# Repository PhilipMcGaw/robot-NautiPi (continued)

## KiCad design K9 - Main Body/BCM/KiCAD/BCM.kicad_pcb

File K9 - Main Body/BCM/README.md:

# K9 Body Control Module (BCM)

## Purpose

Describe the Body Control Module (BCM) hardware, firmware, interfaces, and supporting engineering material contained in this directory.

## Scope

This directory is part of the physical hardware design for K9 within `robot-NautiPi`.

- **NautiPi** is the source of truth for physical hardware design.
- **CuttleOS** is the source of truth for system software, deployment, and runtime behaviour.
- **SquidLink** is used for ROS 2/Gazebo simulation and integration testing.
- **Chartroom** provides the project-wide documentation and repository conventions.

## Contents

Document the files and subdirectories contained here, including their purpose and any significant design or implementation constraints.

## Interfaces

Document important electrical, mechanical, communications, and software interfaces. Include connector names, signal names, protocols, voltage levels, or other interface information where applicable.

## Dependencies

Record dependencies on other hardware assemblies, firmware, software, libraries, or external components where they materially affect this module.

## Status

Use explicit evidence-based status terms such as:

- `planned`
- `implemented`
- `tested`
- `bench-tested`
- `production-validated`

Do not imply a higher level of validation than the available evidence supports.

## Documentation

Keep this README focused on the purpose and boundaries of the directory. Detailed engineering records should be placed in appropriate documentation files within the project.

## Licence

This material is distributed under the licence stated by the repository root `README.md`. See that file for the current licence and repository-wide documentation policy.

## Related repositories

- [CuttleOS](https://github.com/PhilipMcGaw/robot-CuttleOS) — system software and runtime architecture.
- [SquidLink](https://github.com/PhilipMcGaw/robot-SquidLink) — ROS 2/Gazebo simulation and integration testing.
- [Chartroom](https://github.com/PhilipMcGaw/robot-ChartRoom) — project documentation and engineering context, where applicable.

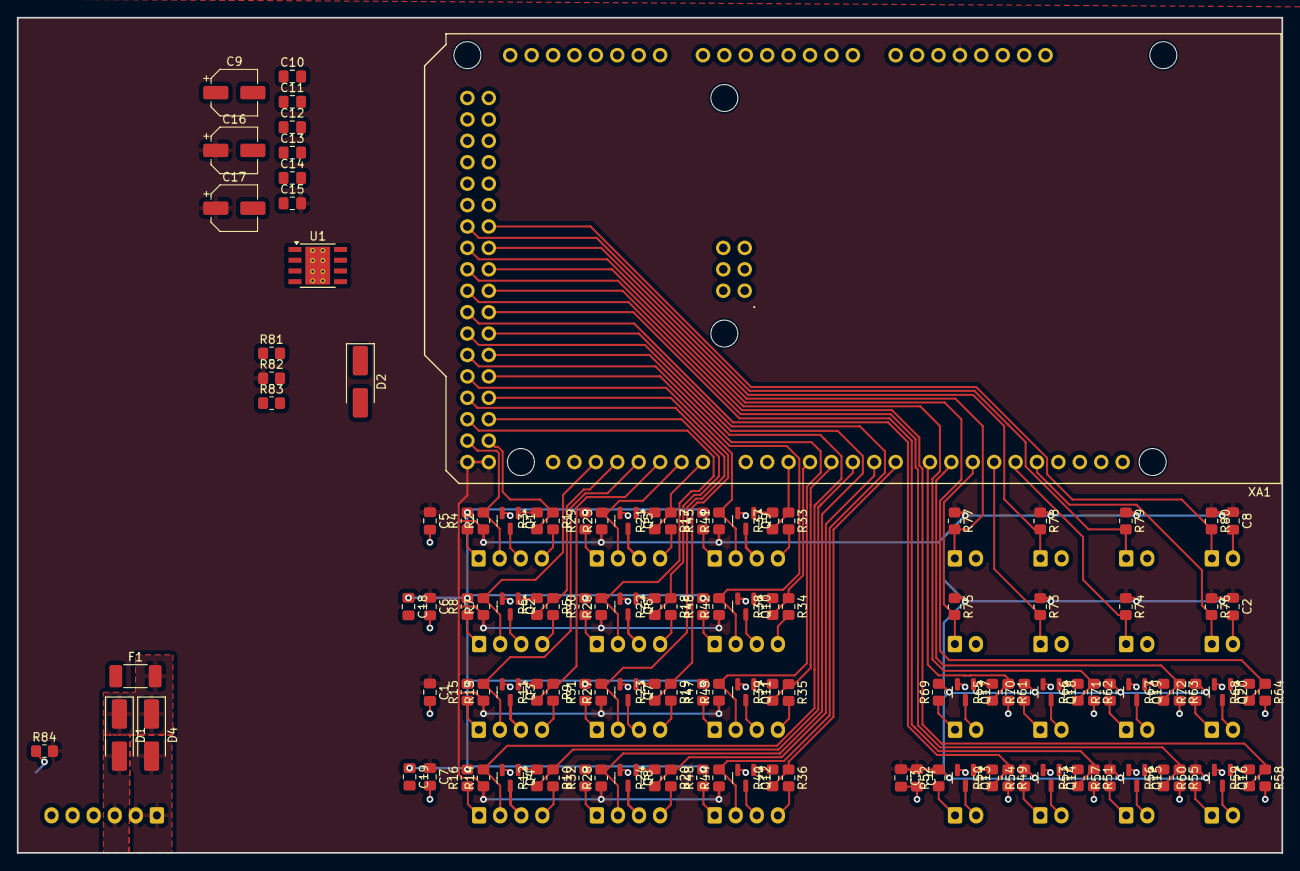
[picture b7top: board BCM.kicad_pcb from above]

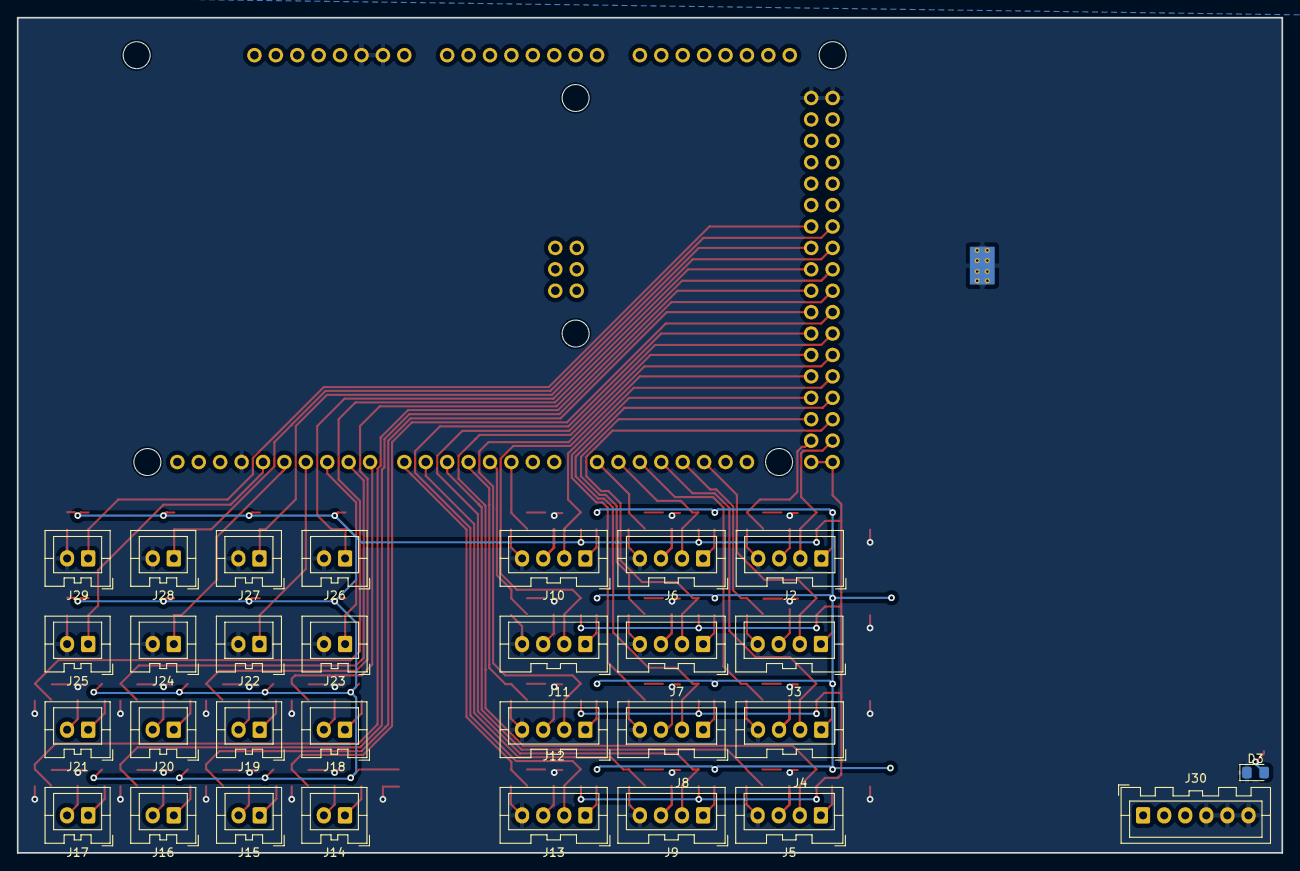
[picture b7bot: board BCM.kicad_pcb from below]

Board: 2 copper layers, 150.0 x 99.1 mm, 159 parts (30 on the bottom side), 114 nets.

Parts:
C1, C2, C3, C4, C5, C6, C7, C8, C18, C19: C_Small; C_0805_2012Metric_Pad1.18x1.45mm_HandSolder
C9: 100μF; CP_Elec_5x5.9
C10: 0.1μF; C_0805_2012Metric_Pad1.18x1.45mm_HandSolder
C11: 10nF; C_0805_2012Metric_Pad1.18x1.45mm_HandSolder
C12: 10pF; C_0805_2012Metric_Pad1.18x1.45mm_HandSolder
C13: 1nF; C_0805_2012Metric_Pad1.18x1.45mm_HandSolder
C14, C15: 0.1uF; C_0805_2012Metric_Pad1.18x1.45mm_HandSolder
C16, C17: 47μF; CP_Elec_5x5.9
D1, D2, D4: SS34; D_SMA_Handsoldering
D3: Green; D_0805_2012Metric_Pad1.15x1.40mm_HandSolder
F1: Fuse; Fuse_2010_5025Metric_Pad1.52x2.65mm_HandSolder
J2: Back_1; JST_XA_B04B-XASK-1_1x04_P2.50mm_Vertical
J3: Back_2; JST_XA_B04B-XASK-1_1x04_P2.50mm_Vertical
J4: Back_3; JST_XA_B04B-XASK-1_1x04_P2.50mm_Vertical
J5: Back_4; JST_XA_B04B-XASK-1_1x04_P2.50mm_Vertical
J6: Back_5; JST_XA_B04B-XASK-1_1x04_P2.50mm_Vertical
J7: Back_6; JST_XA_B04B-XASK-1_1x04_P2.50mm_Vertical
J8: Back_7; JST_XA_B04B-XASK-1_1x04_P2.50mm_Vertical
J9: Back_8; JST_XA_B04B-XASK-1_1x04_P2.50mm_Vertical
J10: Back_9; JST_XA_B04B-XASK-1_1x04_P2.50mm_Vertical
J11: Back_10; JST_XA_B04B-XASK-1_1x04_P2.50mm_Vertical
J12: Back_11; JST_XA_B04B-XASK-1_1x04_P2.50mm_Vertical
J13: Back_12; JST_XA_B04B-XASK-1_1x04_P2.50mm_Vertical
J14: Eye1; JST_XA_B02B-XASK-1_1x02_P2.50mm_Vertical
J15: Eye2; JST_XA_B02B-XASK-1_1x02_P2.50mm_Vertical
J16: Nose; JST_XA_B02B-XASK-1_1x02_P2.50mm_Vertical
J17: S1; JST_XA_B02B-XASK-1_1x02_P2.50mm_Vertical
J18: S2; JST_XA_B02B-XASK-1_1x02_P2.50mm_Vertical
J19: S3; JST_XA_B02B-XASK-1_1x02_P2.50mm_Vertical
J20: S4; JST_XA_B02B-XASK-1_1x02_P2.50mm_Vertical
J21: S5; JST_XA_B02B-XASK-1_1x02_P2.50mm_Vertical
J22: Door2; JST_XA_B02B-XASK-1_1x02_P2.50mm_Vertical
J23: Door1; JST_XA_B02B-XASK-1_1x02_P2.50mm_Vertical
J24: But1; JST_XA_B02B-XASK-1_1x02_P2.50mm_Vertical
J25: But2; JST_XA_B02B-XASK-1_1x02_P2.50mm_Vertical
J26: But3; JST_XA_B02B-XASK-1_1x02_P2.50mm_Vertical
J27: But4; JST_XA_B02B-XASK-1_1x02_P2.50mm_Vertical
J28: But5; JST_XA_B02B-XASK-1_1x02_P2.50mm_Vertical
J29: But6; JST_XA_B02B-XASK-1_1x02_P2.50mm_Vertical
J30: Power; JST_XA_B06B-XASK-1_1x06_P2.50mm_Vertical
Q1, Q2, Q3, Q4, Q5, Q6, Q7, Q8, Q9, Q10, Q11, Q12, Q13, Q14, Q15, Q16, Q17, Q18, Q19, Q20: 2N7002; SOT-23
R1, R2, R5, R7, R9, R10, R13, R14, R17, R18, R19, R20, R25, R26, R27, R28, R33, R34, R35, R36, R41, R42, R43, R44, R49, R51, R55, R58, R61, R62, R63, R64, R73, R74, R75, R76, R77, R78, R79, R80: 10k; R_0805_2012Metric_Pad1.20x1.40mm_HandSolder
R3, R4, R6, R8, R11, R12, R15, R16, R21, R22, R23, R24, R29, R30, R31, R32, R37, R38, R39, R40, R45, R46, R47, R48, R50, R52, R53, R54, R56, R57, R59, R60, R65, R66, R67, R68, R69, R70, R71, R72: 330; R_0805_2012Metric_Pad1.20x1.40mm_HandSolder
R81: 29.4k; R_0805_2012Metric_Pad1.20x1.40mm_HandSolder
R82: 10k2; R_0805_2012Metric_Pad1.20x1.40mm_HandSolder
R83: 1k96; R_0805_2012Metric_Pad1.20x1.40mm_HandSolder
R84: 1k; R_0805_2012Metric_Pad1.20x1.40mm_HandSolder
U1: TPS54331D; TI_SO-PowerPAD-8_ThermalVias
XA1: Arduino_Mega2560_Shield

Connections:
+5V: C1.1, C2.1, C3.1, C4.1, C5.1, C6.1, C7.1, C8.1, C15.2, C16.1, C17.1, R2.1, R7.1, R13.1, R14.1, R25.1, R26.1, R27.1, R28.1, R41.1, R42.1, R43.1, R44.1, R52.2, R54.2, R57.2, R60.2, R69.2, R70.2, R71.2, R72.2, R73.1, R74.1, R75.1, R76.1, R77.1, R78.1, R79.1, R80.1, R82.1, R84.2, XA1.5V1 (5V), XA1.5V3 (5V), XA1.5V4 (5V)
+BATT: D4.2 (A), J30.1, J30.2
+VDC: D1.2 (A), J30.3
/Back Button Connectors/BackButton1: J2.2, R2.2, XA1.D23
/Back Button Connectors/BackButton2: J3.2, R7.2, XA1.D19 (D19_RX1)
/Back Button Connectors/BackButton3: J4.2, R13.2, XA1.D17 (D17_RX2)
/Back Button Connectors/BackButton4: J5.2, R14.2, XA1.D30
/Back Button Connectors/BackButton5: J6.2, R25.2, XA1.D15 (D15_RX3)
/Back Button Connectors/BackButton6: J7.2, R26.2, XA1.D25
/Back Button Connectors/BackButton7: J8.2, R27.2, XA1.D27
/Back Button Connectors/BackButton8: J9.2, R28.2, XA1.D33
/Back Button Connectors/BackButton9: J10.2, R41.2, XA1.D29
/Back Button Connectors/BackButton10: J11.2, R42.2, XA1.D28
/Back Button Connectors/BackButton11: J12.2, R43.2, XA1.D31
/Back Button Connectors/BackButton12: J13.2, R44.2, XA1.D32
/Back Button Connectors/BackLED1: R1.1, R3.1, XA1.D22
/Back Button Connectors/BackLED2: R5.1, R6.1, XA1.D18 (D18_TX1)
/Back Button Connectors/BackLED3: R9.1, R11.1, XA1.D16 (D16_TX2)
/Back Button Connectors/BackLED4: R10.1, R12.1, XA1.D5
/Back Button Connectors/BackLED5: R17.1, R21.1, XA1.D14 (D14_TX3)
/Back Button Connectors/BackLED6: R18.1, R22.1, XA1.D24
/Back Button Connectors/BackLED7: R19.1, R23.1, XA1.D26
/Back Button Connectors/BackLED8: R20.1, R24.1, XA1.D6
/Back Button Connectors/BackLED9: R33.1, R37.1, XA1.D2 (D2_INT0)
/Back Button Connectors/BackLED10: R34.1, R38.1, XA1.D3 (D3_INT1)
/Back Button Connectors/BackLED11: R35.1, R39.1, XA1.D4
/Back Button Connectors/BackLED12: R36.1, R40.1, XA1.D7
/Misc Lights/EyesLight1: R49.1, R50.1, XA1.D35
/Misc Lights/EyesLight2: R51.1, R53.1, XA1.D34
/Misc Lights/NoseLight: R55.1, R56.1, XA1.D37
/Misc Lights/SpaireLight1: R58.1, R59.1, XA1.D36
/Misc Lights/SpaireLight2: R61.1, R65.1, XA1.D8
/Misc Lights/SpaireLight3: R62.1, R66.1, XA1.D39
/Misc Lights/SpaireLight4: R63.1, R67.1, XA1.D9
/Misc Lights/SpaireLight5: R64.1, R68.1, XA1.D38
/Misc Switches/DoorBut1: J23.1, R75.2, XA1.D10
/Misc Switches/DoorBut2: J22.1, R73.2, XA1.D11
/Misc Switches/SpaireBut1: J24.1, R74.2, XA1.D12
/Misc Switches/SpaireBut2: J25.1, R76.2, XA1.D13
/Misc Switches/SpaireBut3: J26.1, R77.2, XA1.D41
/Misc Switches/SpaireBut4: J27.1, R78.2, XA1.D40
/Misc Switches/SpaireBut5: J28.1, R79.2, XA1.D43
/Misc Switches/SpaireBut6: J29.1, R80.2, XA1.D42
Button +Ve: C18.1, C19.1, R4.2, R8.2, R15.2, R16.2, R29.2, R30.2, R31.2, R32.2, R45.2, R46.2, R47.2, R48.2
GND: C1.2, C2.2, C3.2, C4.2, C5.2, C6.2, C7.2, C8.2, C9.2, C10.2, C11.2, C12.1, C13.1, C15.1, C16.2, C17.2, C18.2, C19.2, D2.2 (A), D3.1 (K), J2.4, J3.4, J4.4, J5.4, J6.4, J7.4, J8.4, J9.4, J10.4, J11.4, J12.4, J13.4, J22.2, J23.2, J24.2, J25.2, J26.2, J27.2, J28.2, J29.2, J30.4, J30.5, J30.6, Q1.2 (S), Q2.2 (S), Q3.2 (S), Q4.2 (S), Q5.2 (S), Q6.2 (S), Q7.2 (S), Q8.2 (S), Q9.2 (S), Q10.2 (S), Q11.2 (S), Q12.2 (S), Q13.2 (S), Q14.2 (S), Q15.2 (S), Q16.2 (S), Q17.2 (S), Q18.2 (S), Q19.2 (S), Q20.2 (S), R1.2, R5.2, R9.2, R10.2, R17.2, R18.2, R19.2, R20.2, R33.2, R34.2, R35.2, R36.2, R49.2, R51.2, R55.2, R58.2, R61.2, R62.2, R63.2, R64.2, R83.2, U1.7 (GND), U1.9 (ETPAD), XA1.GND1 (GND), XA1.GND2 (GND), XA1.GND3 (GND), XA1.GND5 (GND), XA1.GND6 (GND)
unnamed: C13.2, R81.2
unnamed: C14.2, D2.1 (K), U1.8 (PH)
unnamed: D3.2 (A), R84.1
unnamed: J2.1, R4.1
unnamed: J2.3, Q1.3 (D)
unnamed: J3.1, R8.1
unnamed: J3.3, Q2.3 (D)
unnamed: J4.1, R15.1
unnamed: J4.3, Q3.3 (D)
unnamed: J5.1, R16.1
unnamed: J5.3, Q4.3 (D)
unnamed: J6.1, R29.1
unnamed: J6.3, Q5.3 (D)
unnamed: J7.1, R30.1
unnamed: J7.3, Q6.3 (D)
unnamed: J8.1, R31.1
unnamed: J8.3, Q7.3 (D)
unnamed: J9.1, R32.1
unnamed: J9.3, Q8.3 (D)
unnamed: J10.1, R45.1
unnamed: J10.3, Q9.3 (D)
unnamed: J11.1, R46.1
unnamed: J11.3, Q10.3 (D)
unnamed: J12.1, R47.1
unnamed: J12.3, Q11.3 (D)
unnamed: J13.1, R48.1
unnamed: J13.3, Q12.3 (D)
unnamed: J14.1, R52.1
unnamed: J14.2, Q13.3 (D)
unnamed: J15.1, R54.1
unnamed: J15.2, Q14.3 (D)
unnamed: J16.1, R57.1
unnamed: J16.2, Q15.3 (D)
unnamed: J17.1, R60.1
unnamed: J17.2, Q16.3 (D)
unnamed: J18.1, R69.1
unnamed: J18.2, Q17.3 (D)
unnamed: J19.1, R70.1
unnamed: J19.2, Q18.3 (D)
unnamed: J20.1, R71.1
unnamed: J20.2, Q19.3 (D)
unnamed: J21.1, R72.1
unnamed: J21.2, Q20.3 (D)
unnamed: Q1.1 (G), R3.2
unnamed: Q2.1 (G), R6.2
unnamed: Q3.1 (G), R11.2
unnamed: Q4.1 (G), R12.2
unnamed: Q5.1 (G), R21.2
unnamed: Q6.1 (G), R22.2
unnamed: Q7.1 (G), R23.2
unnamed: Q8.1 (G), R24.2
unnamed: Q9.1 (G), R37.2
unnamed: Q10.1 (G), R38.2
unnamed: Q11.1 (G), R39.2
unnamed: Q12.1 (G), R40.2
unnamed: Q13.1 (G), R50.2
unnamed: Q14.1 (G), R53.2
unnamed: Q15.1 (G), R56.2
unnamed: Q16.1 (G), R59.2
unnamed: Q17.1 (G), R65.2
unnamed: Q18.1 (G), R66.2
unnamed: Q19.1 (G), R67.2
unnamed: Q20.1 (G), R68.2
unnamed: C14.1, U1.1 (BOOT)
unnamed: C12.2, R81.1, U1.6 (COMP)
unnamed: C11.1, U1.4 (SS)
unnamed: R82.2, R83.1, U1.5 (VSENSE)
Vin+Ve: D1.1 (K), D4.1 (K), F1.2
Vin+Ve (fused): C9.1, C10.1, F1.1, U1.2 (VIN)

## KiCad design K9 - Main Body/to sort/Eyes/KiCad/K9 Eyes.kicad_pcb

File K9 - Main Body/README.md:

# K9 Main Body

This folder contains the K9 main-body hardware and project-reference material.
It is part of [robot-NautiPi](../README.md), not an active software repository.

## Contents

- `BackButtons/` — KiCad design files and supporting material for the rear-button hardware.
- `BCM/` — KiCad design files and embedded material for the K9 body-control module.
- `MotorDriver/` — KiCad design files for the motor-driver hardware.
- `k9/` — K9 project photographs, media, and related reference material.
- `to sort/` — retained K9 design, firmware, mechanical, photographic, and reference material requiring review and classification.
- `OverView.drawio` and `OverView.png` — K9 system overview material.

## Current status

The design and reference material are retained for continued review and
development. Board revisions, assembly, electrical commissioning, actuator
safety testing, and integration with K9 are not recorded as complete here.

Material under `to sort/` is not an approved source of truth. Before using it,
confirm the relevant board revision, firmware revision, wiring, component
values, and physical test evidence.

## Active software and system documentation

The active robot software is maintained in
[robot-CuttleOS](https://github.com/PhilipMcGaw/robot-CuttleOS). The independent
ROS 2/Gazebo simulation and integration-test environment is maintained in
[robot-SquidLink](https://github.com/PhilipMcGaw/robot-SquidLink). Cross-project
architecture, engineering rationale, and project-wide documentation are
maintained in [Chartroom](https://chartroom.philipmcgaw.com/).

Hardware interfaces, robot profiles, deployment, and validation status are
defined by the current engineering documentation rather than by historical
material retained in this folder.

## Licensing

See the parent [NautiPi licensing map](../LICENSES.md). Hardware design files
are covered by CERN-OHL-S 2.0; project software, documentation, and reference
material are covered by CC BY-NC-SA 4.0, subject to any separate third-party
notices.

## People who have helped

- Philip 'Skippy' McGaw - <philip@mcgaw.eu> - [philipmcgaw.com](https://philipmcgaw.com)
- Tamarisk 'NotQuiteHere' McGaw - <tamarisk@mcgaw.eu> - [tamarisk.it](https://tamarisk.it)
- Bob 'thinkl33t' Clough - <bob@clough.me> - [thinkl33t.co.uk](https://thinkl33t.co.uk)

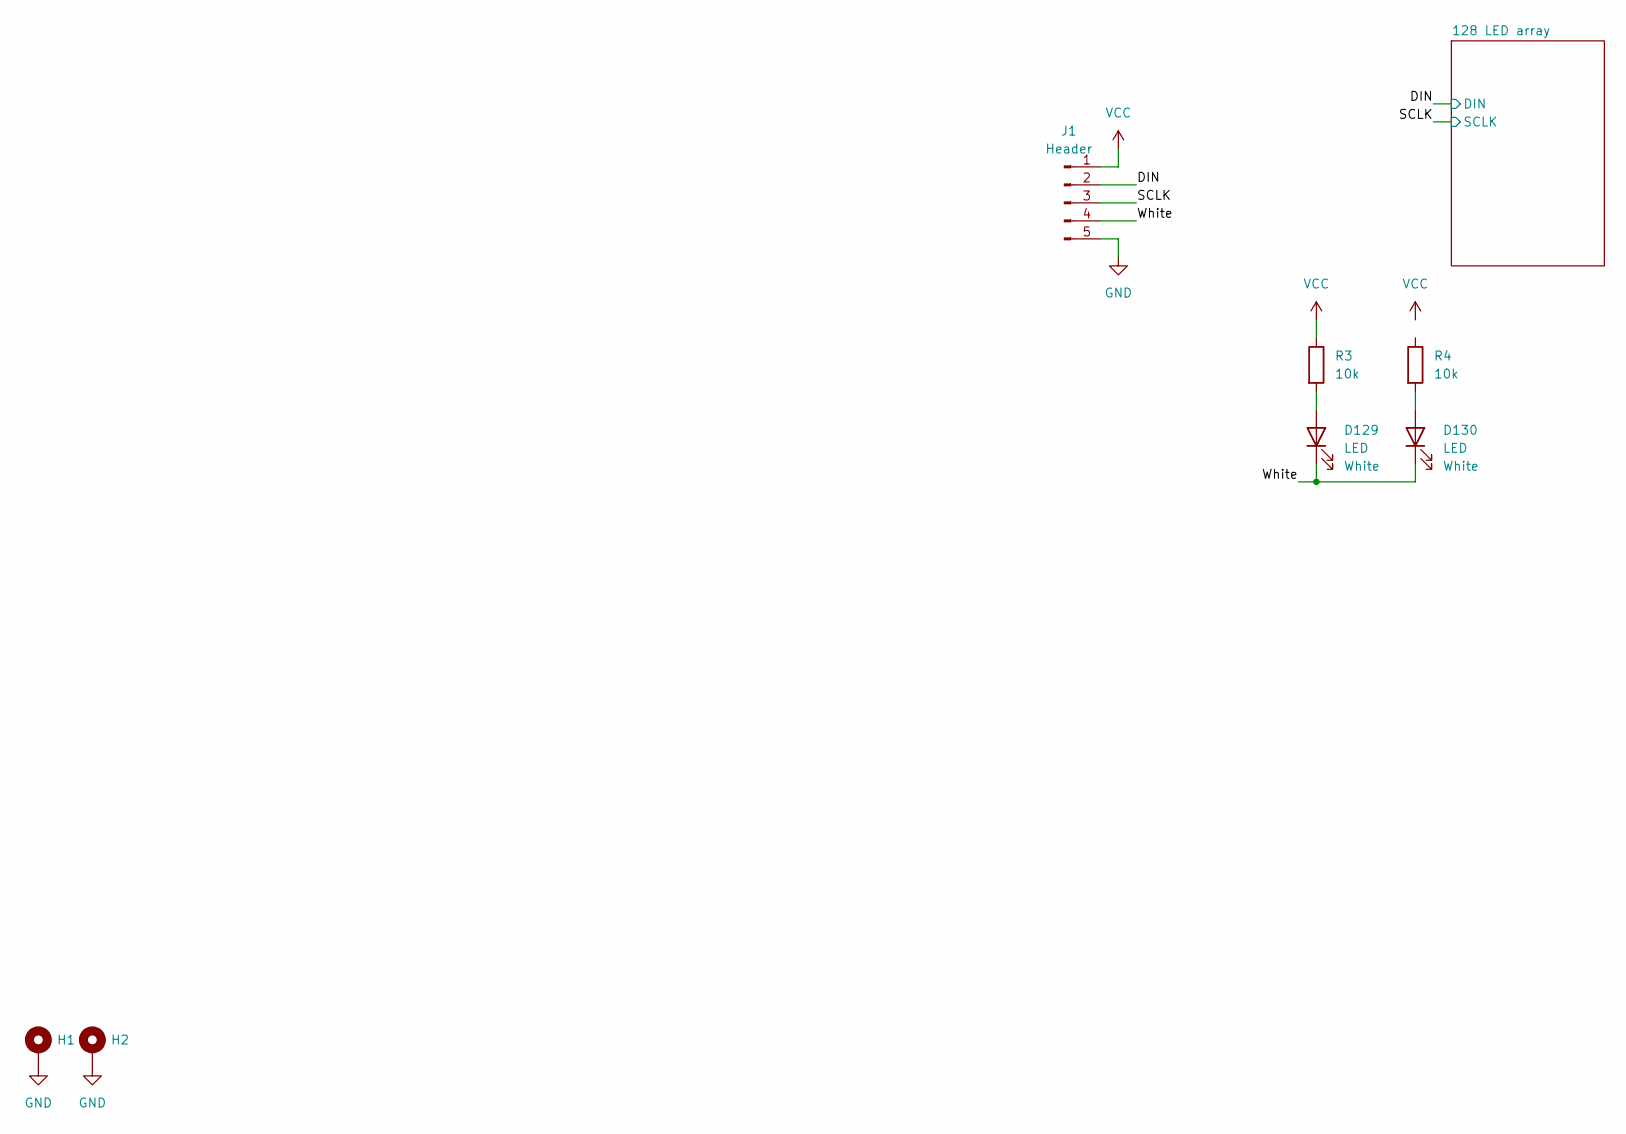
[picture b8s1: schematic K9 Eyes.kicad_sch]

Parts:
D129, D130: LED; LED_1206_3216Metric_Pad1.42x1.75mm_HandSolder
H1, H2: MountingHole_Pad; MountingHole_3.5mm_Pad
J1: Header; PinHeader_1x05_P2.54mm_Vertical
R3, R4: 10k; R_0805_2012Metric_Pad1.20x1.40mm_HandSolder

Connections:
/DIN: J1.2; also elsewhere on the board
/SCLK: J1.3; also elsewhere on the board
/White: D129.1 (K), D130.1 (K), J1.4
GND: H1.1, H2.1, J1.5; also elsewhere on the board
unnamed: D129.2 (A), R3.2
unnamed: D130.2 (A), R4.2
VCC: J1.1, R3.1; also elsewhere on the board

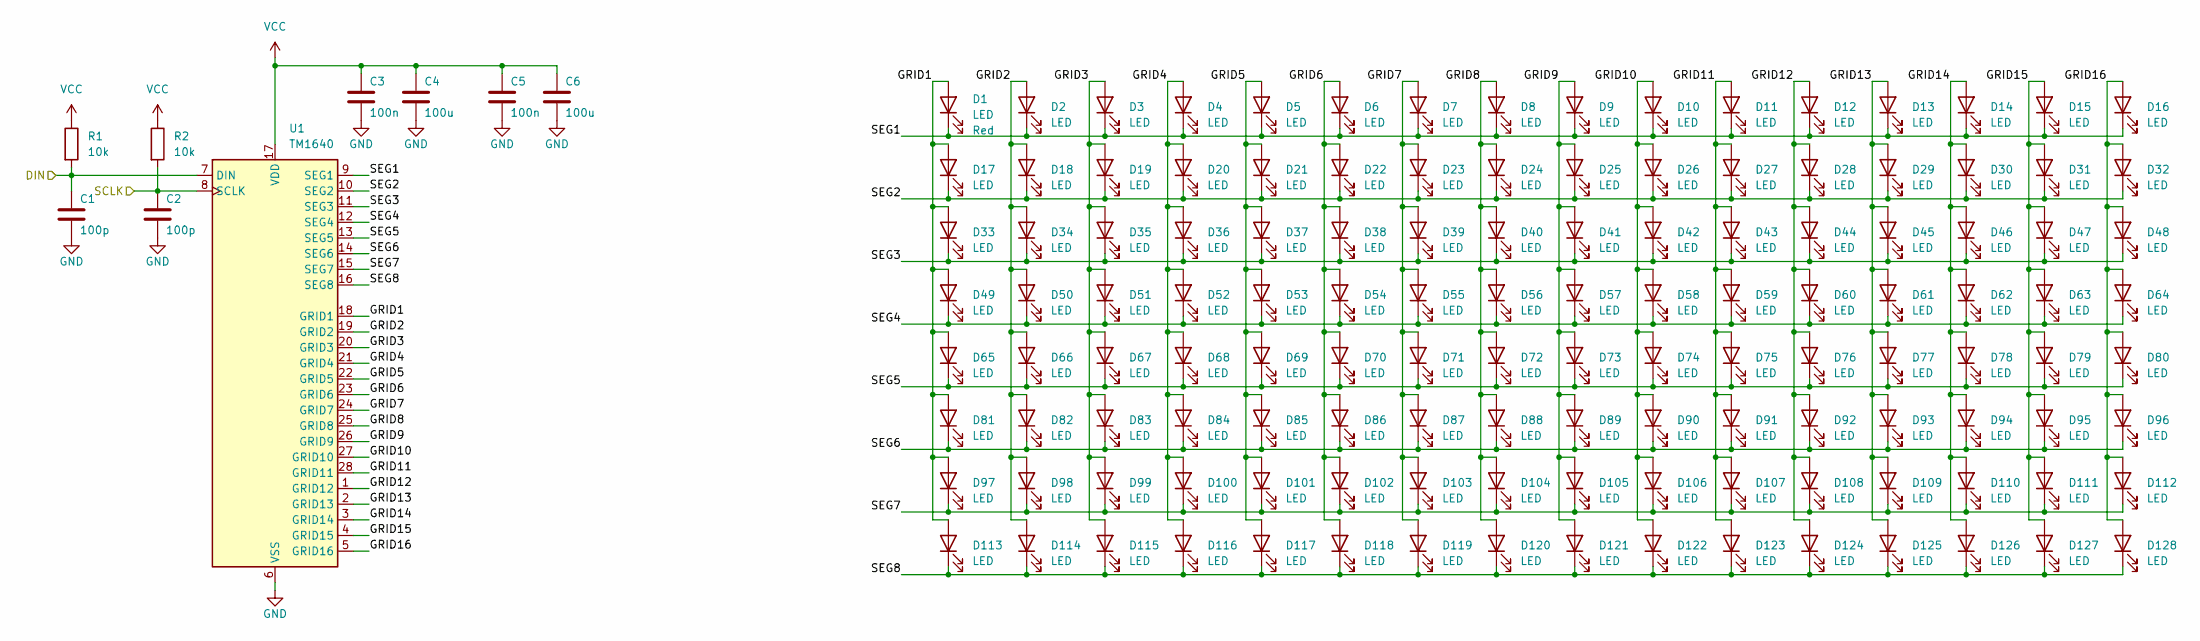
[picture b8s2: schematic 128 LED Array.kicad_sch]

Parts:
C1, C2: 100p; C_0805_2012Metric_Pad1.18x1.45mm_HandSolder
C3, C5: 100n; C_0805_2012Metric_Pad1.18x1.45mm_HandSolder
C4, C6: 100u; C_0805_2012Metric_Pad1.18x1.45mm_HandSolder
D1, D2, D3, D4, D5, D6, D7, D8, D9, D10, D11, D12, D13, D14, D15, D16, D17, D18, D19, D20, D21, D22, D23, D24, D25, D26, D27, D28, D29, D30, D31, D32, D33, D34, D35, D36, D37, D38, D39, D40, D41, D42, D43, D44, D45, D46, D47, D48, D49, D50, D51, D52, D53, D54, D55, D56, D57, D58, D59, D60, D61, D62, D63, D64, D65, D66, D67, D68, D69, D70, D71, D72, D73, D74, D75, D76, D77, D78, D79, D80, D81, D82, D83, D84, D85, D86, D87, D88, D89, D90, D91, D92, D93, D94, D95, D96, D97, D98, D99, D100, D101, D102, D103, D104, D105, D106, D107, D108, D109, D110, D111, D112, D113, D114, D115, D116, D117, D118, D119, D120, D121, D122, D123, D124, D125, D126, D127, D128: LED; LED_1206_3216Metric_Pad1.42x1.75mm_HandSolder
R1, R2: 10k; R_0805_2012Metric_Pad1.20x1.40mm_HandSolder
U1: TM1640; SOIC-28W_7.5x17.9mm_P1.27mm

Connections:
/128 LED array/GRID1: D1.2 (A), D17.2 (A), D33.2 (A), D49.2 (A), D65.2 (A), D81.2 (A), D97.2 (A), D113.2 (A), U1.18 (GRID1)
/128 LED array/GRID2: D2.2 (A), D18.2 (A), D34.2 (A), D50.2 (A), D66.2 (A), D82.2 (A), D98.2 (A), D114.2 (A), U1.19 (GRID2)
/128 LED array/GRID3: D3.2 (A), D19.2 (A), D35.2 (A), D51.2 (A), D67.2 (A), D83.2 (A), D99.2 (A), D115.2 (A), U1.20 (GRID3)
/128 LED array/GRID4: D4.2 (A), D20.2 (A), D36.2 (A), D52.2 (A), D68.2 (A), D84.2 (A), D100.2 (A), D116.2 (A), U1.21 (GRID4)
/128 LED array/GRID5: D5.2 (A), D21.2 (A), D37.2 (A), D53.2 (A), D69.2 (A), D85.2 (A), D101.2 (A), D117.2 (A), U1.22 (GRID5)
/128 LED array/GRID6: D6.2 (A), D22.2 (A), D38.2 (A), D54.2 (A), D70.2 (A), D86.2 (A), D102.2 (A), D118.2 (A), U1.23 (GRID6)
/128 LED array/GRID7: D7.2 (A), D23.2 (A), D39.2 (A), D55.2 (A), D71.2 (A), D87.2 (A), D103.2 (A), D119.2 (A), U1.24 (GRID7)
/128 LED array/GRID8: D8.2 (A), D24.2 (A), D40.2 (A), D56.2 (A), D72.2 (A), D88.2 (A), D104.2 (A), D120.2 (A), U1.25 (GRID8)
/128 LED array/GRID9: D9.2 (A), D25.2 (A), D41.2 (A), D57.2 (A), D73.2 (A), D89.2 (A), D105.2 (A), D121.2 (A), U1.26 (GRID9)
/128 LED array/GRID10: D10.2 (A), D26.2 (A), D42.2 (A), D58.2 (A), D74.2 (A), D90.2 (A), D106.2 (A), D122.2 (A), U1.27 (GRID10)
/128 LED array/GRID11: D11.2 (A), D27.2 (A), D43.2 (A), D59.2 (A), D75.2 (A), D91.2 (A), D107.2 (A), D123.2 (A), U1.28 (GRID11)
/128 LED array/GRID12: D12.2 (A), D28.2 (A), D44.2 (A), D60.2 (A), D76.2 (A), D92.2 (A), D108.2 (A), D124.2 (A), U1.1 (GRID12)
/128 LED array/GRID13: D13.2 (A), D29.2 (A), D45.2 (A), D61.2 (A), D77.2 (A), D93.2 (A), D109.2 (A), D125.2 (A), U1.2 (GRID13)
/128 LED array/GRID14: D14.2 (A), D30.2 (A), D46.2 (A), D62.2 (A), D78.2 (A), D94.2 (A), D110.2 (A), D126.2 (A), U1.3 (GRID14)
/128 LED array/GRID15: D15.2 (A), D31.2 (A), D47.2 (A), D63.2 (A), D79.2 (A), D95.2 (A), D111.2 (A), D127.2 (A), U1.4 (GRID15)
/128 LED array/GRID16: D16.2 (A), D32.2 (A), D48.2 (A), D64.2 (A), D80.2 (A), D96.2 (A), D112.2 (A), D128.2 (A), U1.5 (GRID16)
/128 LED array/SEG1: D1.1 (K), D2.1 (K), D3.1 (K), D4.1 (K), D5.1 (K), D6.1 (K), D7.1 (K), D8.1 (K), D9.1 (K), D10.1 (K), D11.1 (K), D12.1 (K), D13.1 (K), D14.1 (K), D15.1 (K), D16.1 (K), U1.9 (SEG1)
/128 LED array/SEG2: D17.1 (K), D18.1 (K), D19.1 (K), D20.1 (K), D21.1 (K), D22.1 (K), D23.1 (K), D24.1 (K), D25.1 (K), D26.1 (K), D27.1 (K), D28.1 (K), D29.1 (K), D30.1 (K), D31.1 (K), D32.1 (K), U1.10 (SEG2)
/128 LED array/SEG3: D33.1 (K), D34.1 (K), D35.1 (K), D36.1 (K), D37.1 (K), D38.1 (K), D39.1 (K), D40.1 (K), D41.1 (K), D42.1 (K), D43.1 (K), D44.1 (K), D45.1 (K), D46.1 (K), D47.1 (K), D48.1 (K), U1.11 (SEG3)
/128 LED array/SEG4: D49.1 (K), D50.1 (K), D51.1 (K), D52.1 (K), D53.1 (K), D54.1 (K), D55.1 (K), D56.1 (K), D57.1 (K), D58.1 (K), D59.1 (K), D60.1 (K), D61.1 (K), D62.1 (K), D63.1 (K), D64.1 (K), U1.12 (SEG4)
/128 LED array/SEG5: D65.1 (K), D66.1 (K), D67.1 (K), D68.1 (K), D69.1 (K), D70.1 (K), D71.1 (K), D72.1 (K), D73.1 (K), D74.1 (K), D75.1 (K), D76.1 (K), D77.1 (K), D78.1 (K), D79.1 (K), D80.1 (K), U1.13 (SEG5)
/128 LED array/SEG6: D81.1 (K), D82.1 (K), D83.1 (K), D84.1 (K), D85.1 (K), D86.1 (K), D87.1 (K), D88.1 (K), D89.1 (K), D90.1 (K), D91.1 (K), D92.1 (K), D93.1 (K), D94.1 (K), D95.1 (K), D96.1 (K), U1.14 (SEG6)
/128 LED array/SEG7: D97.1 (K), D98.1 (K), D99.1 (K), D100.1 (K), D101.1 (K), D102.1 (K), D103.1 (K), D104.1 (K), D105.1 (K), D106.1 (K), D107.1 (K), D108.1 (K), D109.1 (K), D110.1 (K), D111.1 (K), D112.1 (K), U1.15 (SEG7)
/128 LED array/SEG8: D113.1 (K), D114.1 (K), D115.1 (K), D116.1 (K), D117.1 (K), D118.1 (K), D119.1 (K), D120.1 (K), D121.1 (K), D122.1 (K), D123.1 (K), D124.1 (K), D125.1 (K), D126.1 (K), D127.1 (K), D128.1 (K), U1.16 (SEG8)
/DIN: C1.1, R1.2, U1.7 (DIN); also elsewhere on the board
/SCLK: C2.1, R2.2, U1.8 (SCLK); also elsewhere on the board
GND: C1.2, C2.2, C3.2, C4.2, C5.2, C6.2, U1.6 (VSS); also elsewhere on the board
VCC: C3.1, C4.1, C5.1, C6.1, R1.1, R2.1, U1.17 (VDD); also elsewhere on the board

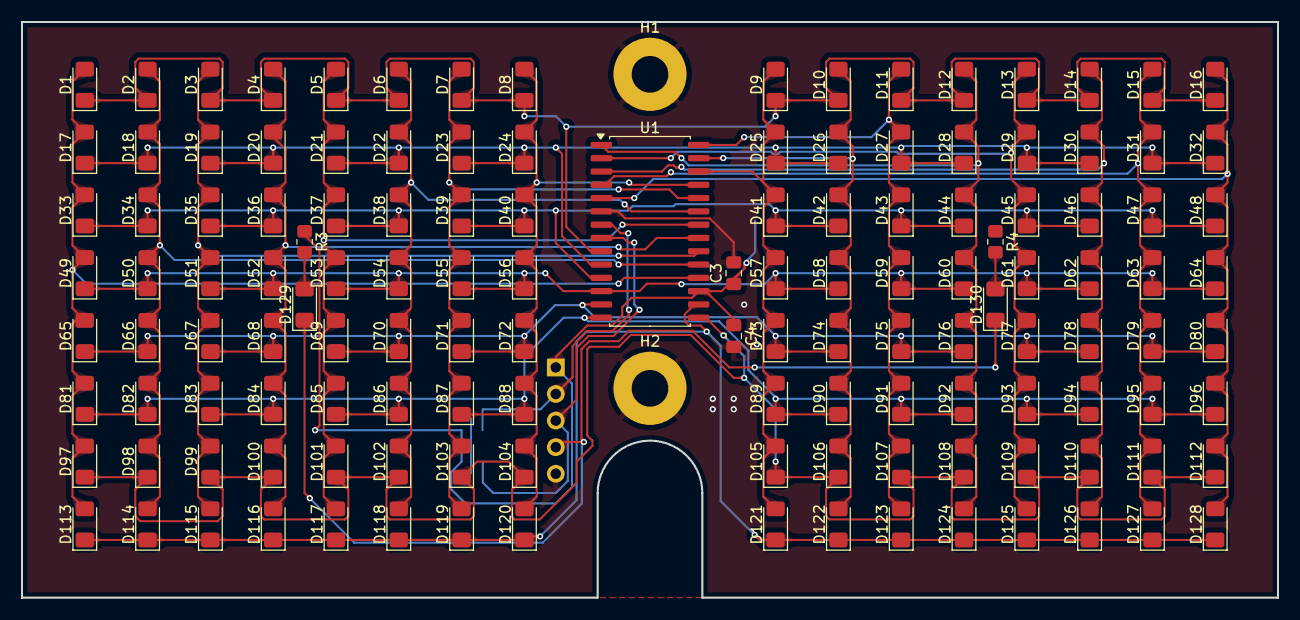
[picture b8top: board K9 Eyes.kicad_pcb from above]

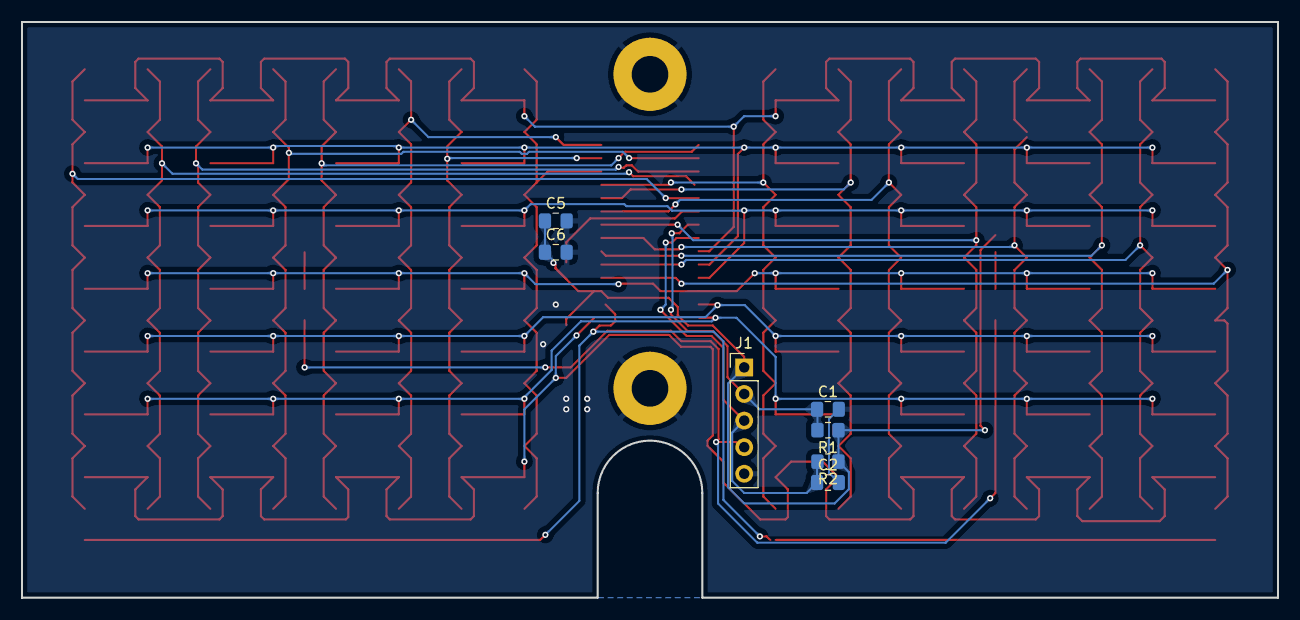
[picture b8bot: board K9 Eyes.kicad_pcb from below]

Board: 2 copper layers, 120.0 x 55.0 mm, 144 parts (7 on the bottom side), 31 nets.
